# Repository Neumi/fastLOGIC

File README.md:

# fastLOGIC! open-source (industrial) logic controller

### An affordable Arduino-based board designed for straightforward (industrial) logic control, ideal for building small-scale automation and control solutions.
FastLOGIC! is designed to cater to the automation needs of various applications, especially those with modest logic requirements. Its purpose is to streamline smaller projects by eliminating the need for excessive error-prone breadboarding while retaining flexibility and adaptability.

Use cases could be one of these: 
- a programmable fridge controller
- water level-dependent pump controller
- a timer that is triggered by a button
- an actuator that activates and moves to an end stop upon receiving a triggering input
- some sensor data you need to display
- a water level sensor/alarm
- you get the idea

# Software

The Arduino [library](https://github.com/Neumi/fastLOGIC/tree/main/software/library/fastLOGIC) can be used to get started. A few example sketches show what fastLOGIC! is capable of, how to read sensor data and how to write outputs to the LEDs and relays.

The library covers most cases, but if you want to write or read directly from or to the pins:
```cpp
// fastLOGIC! pin mapping
DIGITAL_IN_A = D2;
DIGITAL_IN_B = D3;
RELAY_A_OUT = D5;
RELAY_B_OUT = D4;
TM1637_SCK = D6;
TM1637_DIO = D7;
DS18B20_DATA = D9;
LED_B_OUT = D10;
LED_A_OUT = D13;
VOLTAGE_SENS_IN = A0;
BUTTONS_IN = A1;
ANALOG_IN_A = A2;
ANALOG_IN_B = A3;
```

If you want to use the **7-segment display**, use this [library](https://github.com/avishorp/TM1637).

The part numbers in the KiCAD files are LCSC part numbers. This means you can order directly from JLCPCB using the manufacturing files in the [production folder](https://github.com/Neumi/fastLOGIC/tree/main/hardware/version001/fastLOGIC/production).
I typically opt for SMT parts exclusively due to the high cost associated with THT assembly and also because not all the required parts are readily available in stock.

# Hardware
The placement is largely self-explanatory. If you find yourself uncertain, you can refer to the images provided below or utilize the 3D view feature in KiCAD for further clarification.

###  The only hardware parts you need:
- [relais 5V](https://de.aliexpress.com/item/1005006065653383.html)
- [4-bit Common Anode Display](https://de.aliexpress.com/item/1005006101748128.html)
- [JST connectors 3pin + 4pin](https://de.aliexpress.com/item/4000120545240.html)
- [Screw terminals 2pin + 3pin](https://de.aliexpress.com/item/1005005194957825.html)
- [USB connector Type A](https://de.aliexpress.com/item/1005004679855929.html)
- [Case](https://de.aliexpress.com/item/32760647473.html)
- an [ISP](https://de.aliexpress.com/item/1005006164091737.html) or Arduino in ISP mode to burn the Bootloader
- three 5mm (M3) screws

### Optional:
- [XGZP6847a pressure sensor](https://de.aliexpress.com/item/1005003768236942.html)
- [High-pressure sensor](https://de.aliexpress.com/item/1005005510454084.html)
- [DS18B20 temperature sensor](https://de.aliexpress.com/item/1005005973956237.html)

## Assembly

## Video:

Follow the project on [hackaday.io](https://hackaday.io/project/194762-fastlogic-open-source-industrial-logic-control)!

### Enjoy the project, but keep in mind:
* **The project is still under development and is currently in the prototype stage! Keep an eye out for updates!**
* **This also implies that not all functions are guaranteed to work flawlessly and may not be entirely safe**
* **Avoid unsupervised usage in a production environment. Utilize at your own risk**
* **Ensure input voltage is between the range of 12 to 25V. (Currently lacking reverse polarity protection)**
* **Do not use the relay to switch mains voltage! It's suitable only for low voltage and currents below 5A**

### Happy building + coding!

## Big thanks to the sponsors of this project!

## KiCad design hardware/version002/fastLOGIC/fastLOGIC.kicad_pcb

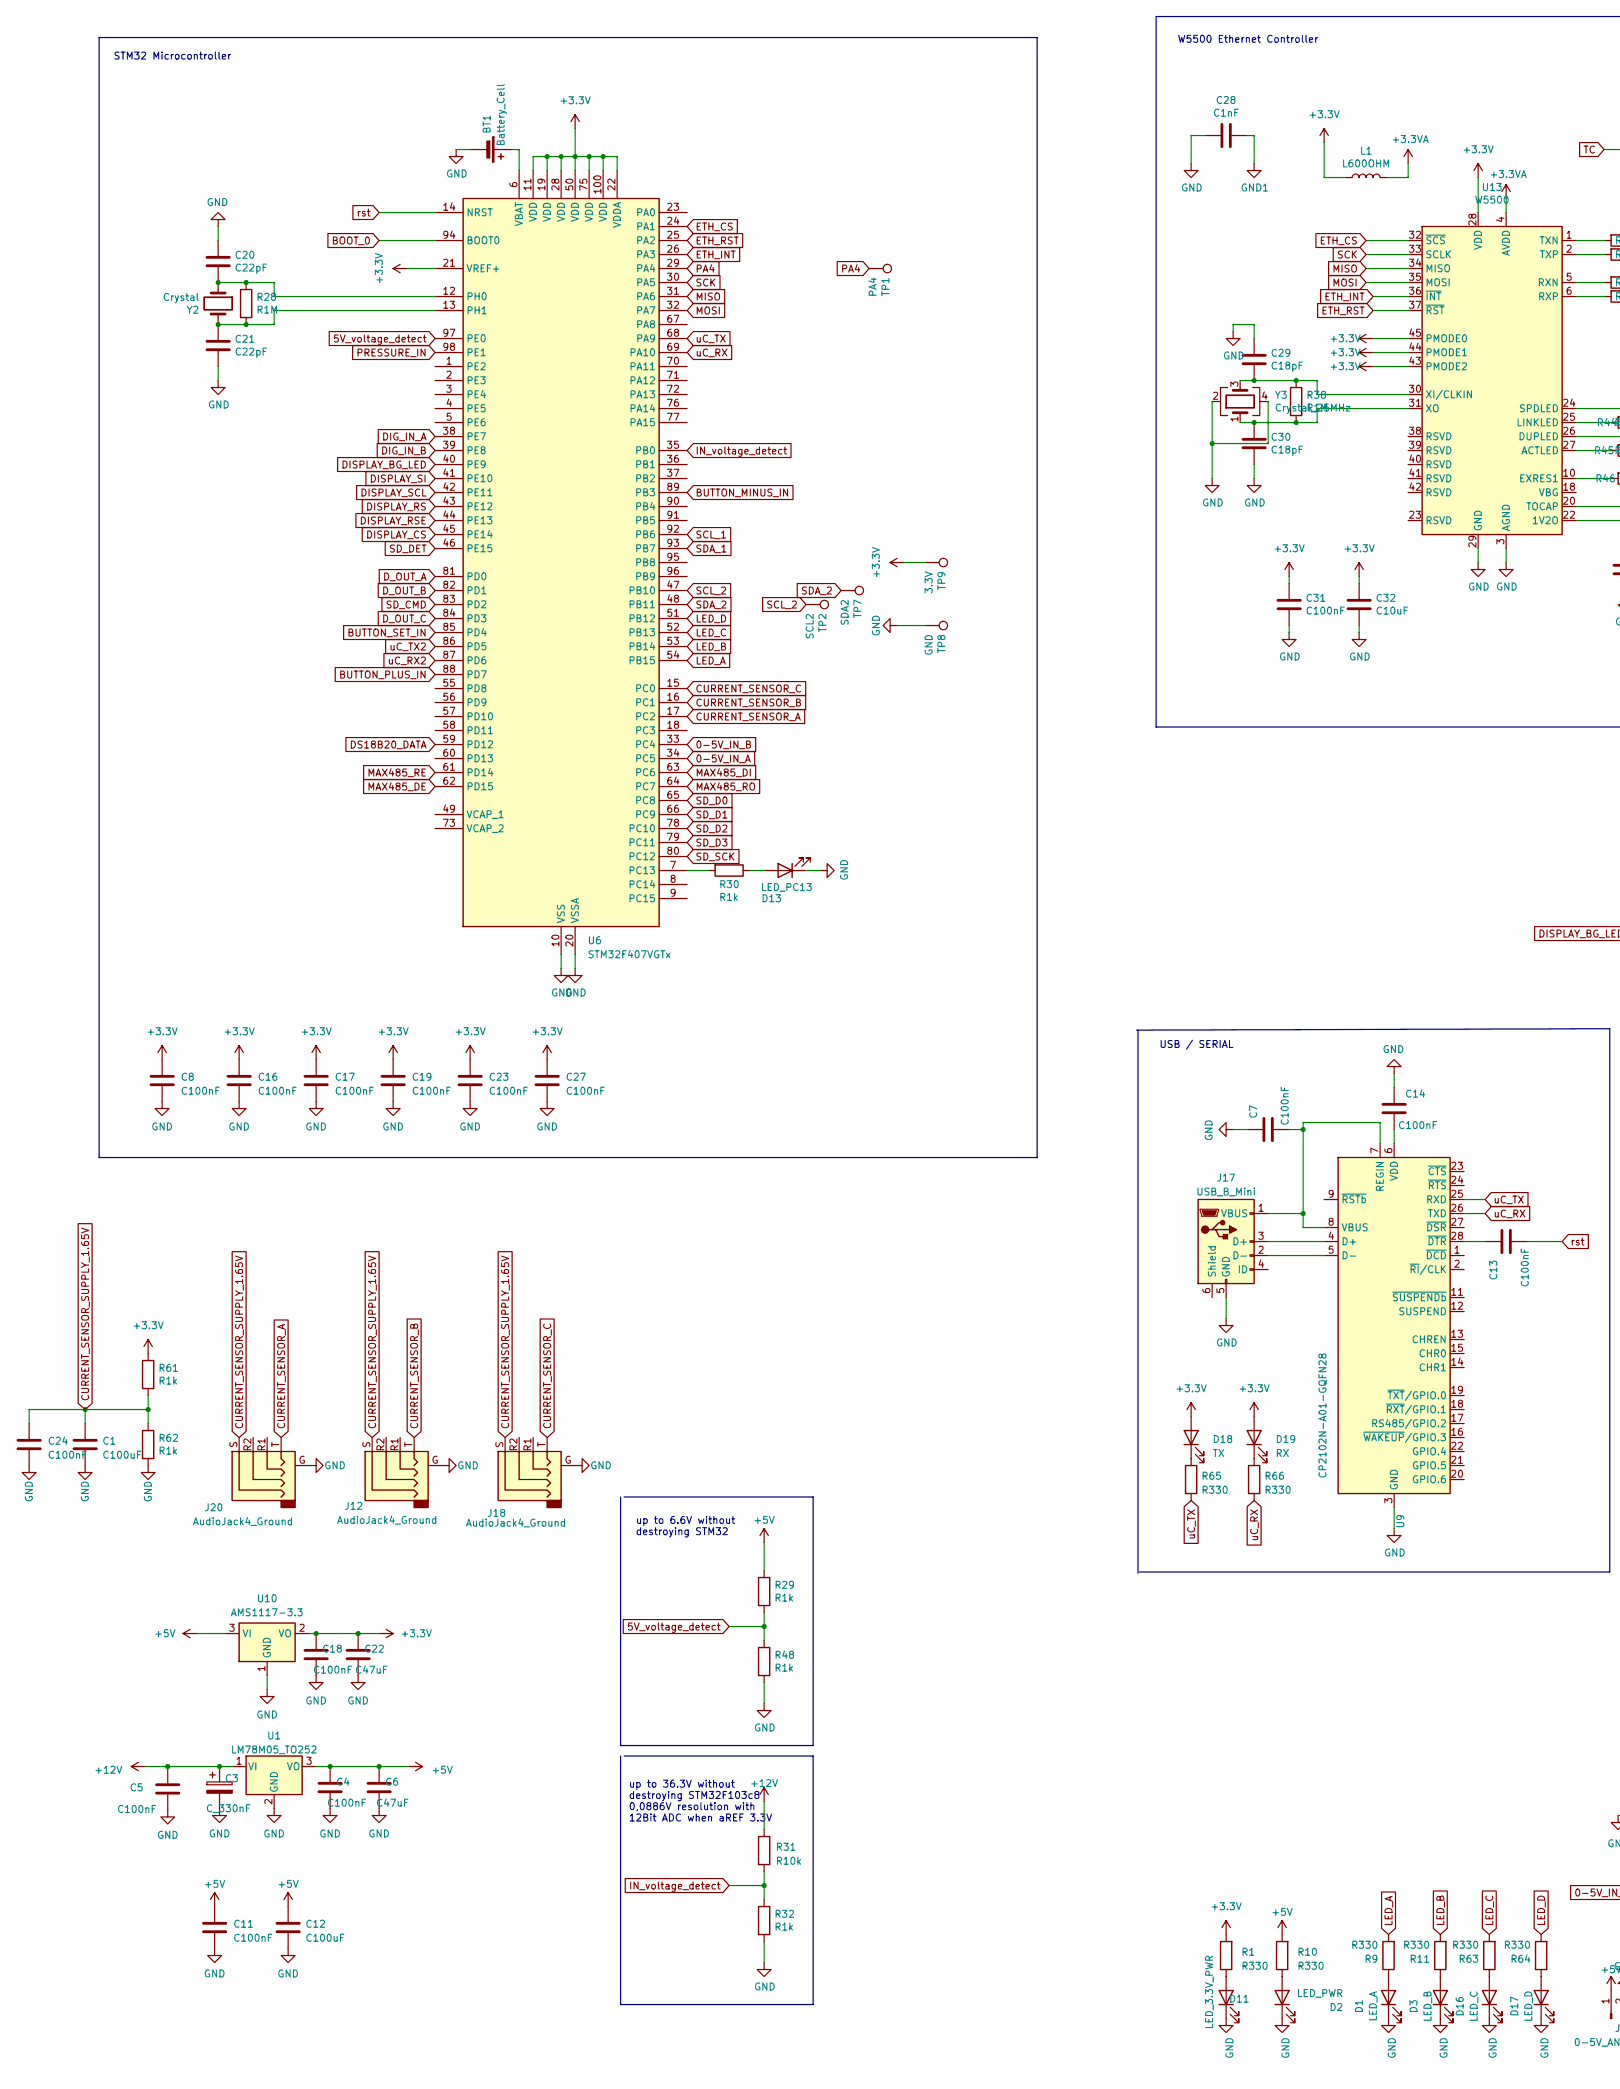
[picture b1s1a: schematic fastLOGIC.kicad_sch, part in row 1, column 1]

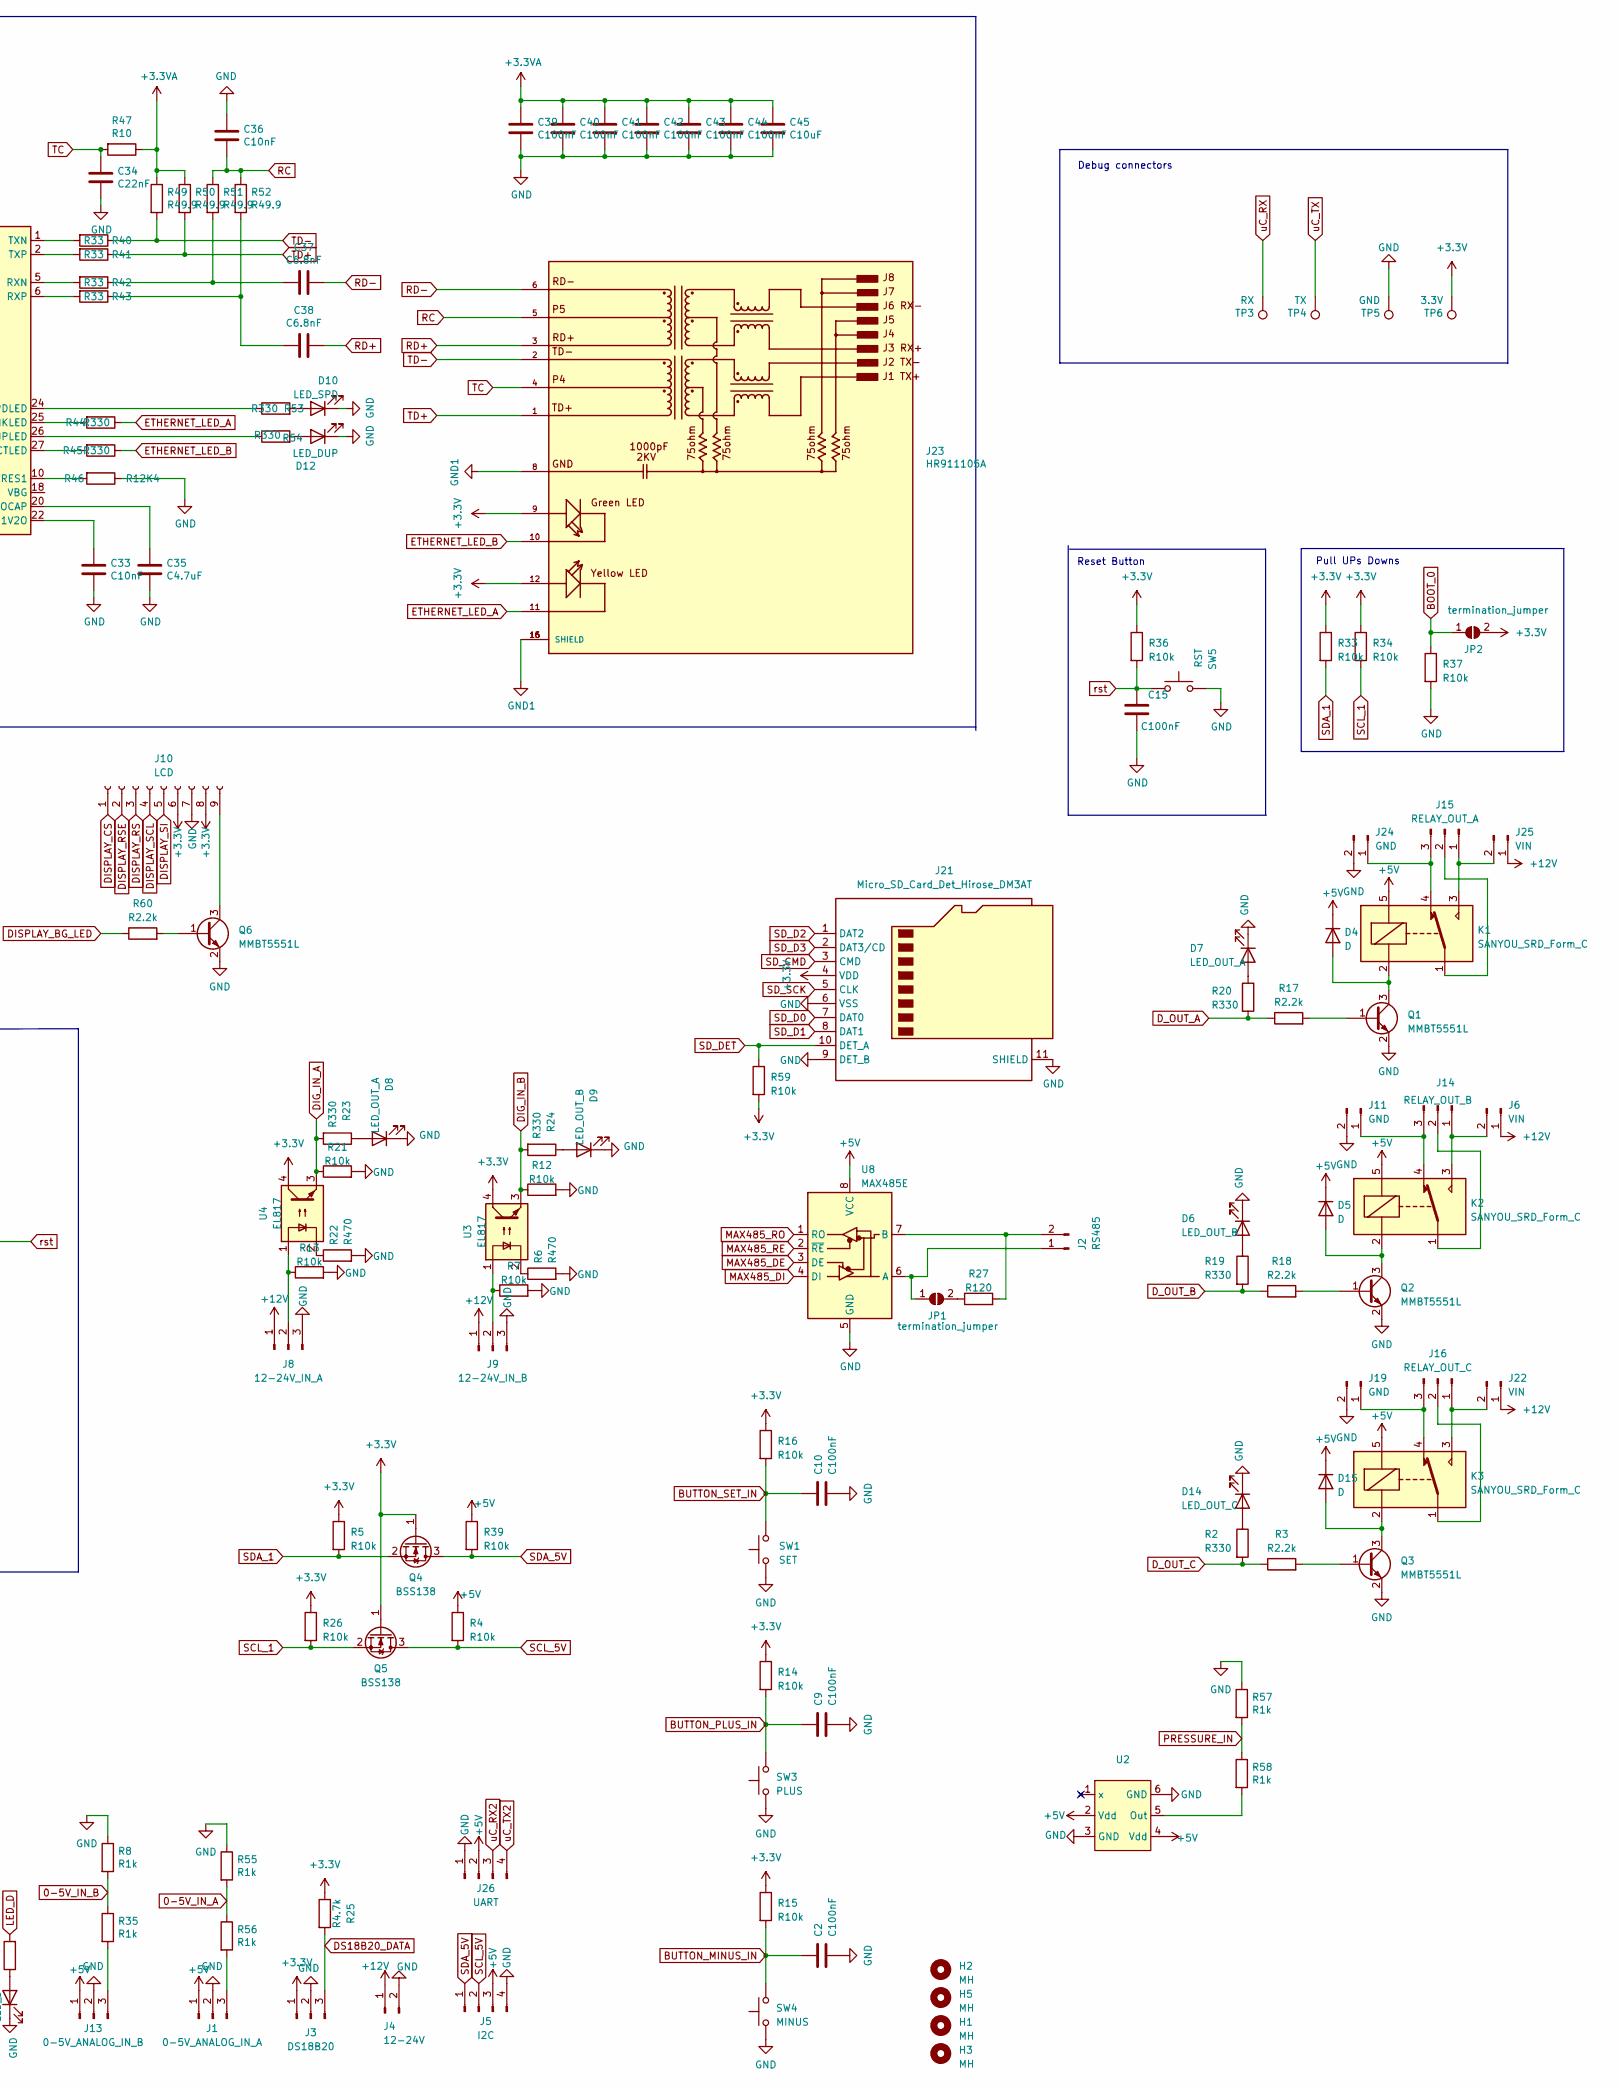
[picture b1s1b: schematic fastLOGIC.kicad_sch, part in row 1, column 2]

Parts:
BT1: Battery_Cell; BatteryHolder_Keystone_1060_1x2032; LCSC C70377
C1, C12: C100uF; C_1206_3216Metric; LCSC C15008
C2, C7, C8, C9, C10, C11, C13, C14, C15, C16, C17, C19, C23, C24, C27, C31: C100nF; C_0603_1608Metric; LCSC C14663
C3: C_330nF; CP_Elec_4x5.4; LCSC C264238
C4, C5, C18: C100nF; C_1206_3216Metric; LCSC C24497
C6, C22: C47uF; C_1206_3216Metric; LCSC C96123
C20, C21: C22pF; C_0402_1005Metric; LCSC C1555
C28: C1nF; C_1206_3216Metric; LCSC C9196
C29, C30: C18pF; C_0402_1005Metric; LCSC C1549
C32, C45: C10uF; C_0805_2012Metric; LCSC C15850
C33: C10nF; C_0402_1005Metric; LCSC C15195
C34: C22nF; C_0603_1608Metric; LCSC C21122
C35: C4.7uF; C_0402_1005Metric; LCSC C23733
C36: C10nF; C_0603_1608Metric; LCSC C57112
C37, C38: C6.8nF; C_0402_1005Metric; LCSC C1542
C39, C40, C41, C42, C43, C44: C100nF; C_0402_1005Metric; LCSC C307331
D1: LED_A; LED_0805_2012Metric; LCSC C2297
D2: LED_PWR; LED_0805_2012Metric; LCSC C84256
D3: LED_B; LED_0805_2012Metric; LCSC C2297
D4, D5, D15: D; D_SMA; LCSC C22452
D6, D9: LED_OUT_B; LED_0805_2012Metric; LCSC C2296
D7, D8: LED_OUT_A; LED_0805_2012Metric; LCSC C2296
D10: LED_SPD; LED_0805_2012Metric; LCSC C2296
D11: LED_3.3V_PWR; LED_0805_2012Metric; LCSC C2296
D12: LED_DUP; LED_0805_2012Metric; LCSC C2296
D13: LED_PC13; LED_0805_2012Metric; LCSC C84256
D14: LED_OUT_C; LED_0805_2012Metric; LCSC C2296
D16: LED_C; LED_0805_2012Metric; LCSC C2297
D17: LED_D; LED_0805_2012Metric; LCSC C2297
D18: TX; LED_0805_2012Metric; LCSC C2297
D19: RX; LED_0805_2012Metric; LCSC C2297
H1, H2, H3, H5: MH; MountingHole_3.2mm_M3_DIN965
J1: 0-5V_ANALOG_IN_A; JST_EH_S3B-EH_1x03_P2.50mm_Horizontal; LCSC C157928
J2: RS485; TerminalBlock_4Ucon_1x02_P3.50mm_Vertical; LCSC C2997509
J3: DS18B20; JST_EH_S3B-EH_1x03_P2.50mm_Horizontal; LCSC C157928
J4: 12-24V; TerminalBlock_4Ucon_1x02_P3.50mm_Vertical; LCSC C2997509
J5: I2C; JST_EH_S4B-EH_1x04_P2.50mm_Horizontal; LCSC C157925
J6, J22, J25: VIN; PinHeader_1x02_P2.54mm_Vertical
J8: 12-24V_IN_A; TerminalBlock_4Ucon_1x03_P3.50mm_Vertical; LCSC C2997510
J9: 12-24V_IN_B; TerminalBlock_4Ucon_1x03_P3.50mm_Vertical; LCSC C2997510
J10: LCD; LCD_GMG12864-06D
J11, J19, J24: GND; PinHeader_1x02_P2.54mm_Vertical
J12, J18, J20: AudioJack4_Ground; Jack_3.5mm_PJ320E_Horizontal
J13: 0-5V_ANALOG_IN_B; JST_EH_S3B-EH_1x03_P2.50mm_Horizontal; LCSC C157928
J14: RELAY_OUT_B; TerminalBlock_4Ucon_1x03_P3.50mm_Vertical; LCSC C2997510
J15: RELAY_OUT_A; TerminalBlock_4Ucon_1x03_P3.50mm_Vertical; LCSC C2997510
J16: RELAY_OUT_C; TerminalBlock_4Ucon_1x03_P3.50mm_Vertical; LCSC C2997510
J17: USB_B_Mini; USB_Mini-B_Tensility_54-00023_Vertical; LCSC C6331167
J21: Micro_SD_Card_Det_Hirose_DM3AT; microSD_HC_Hirose_DM3AT-SF-PEJM5; LCSC C114218
J23: HR911105A; RJ45_Hanrun_HR911105A_Horizontal; PARTREV A; LCSC C12074
J26: UART; JST_EH_B4B-EH-A_1x04_P2.50mm_Vertical; LCSC C157925
JP1, JP2: termination_jumper; PinHeader_1x02_P2.54mm_Vertical
K1, K2, K3: SANYOU_SRD_Form_C; Relay_SPDT_SANYOU_SRD_Series_Form_C; LCSC C35449
L1: L600OHM; L_0805_2012Metric; LCSC C1017
Q1, Q2, Q3, Q6: MMBT5551L; SOT-23; LCSC C2145
Q4, Q5: BSS138; SOT-23; LCSC C112239
R1, R2, R9, R10, R11, R19, R20, R23, R24, R44, R45, R53, R54, R63, R64, R65, R66: R330; R_0603_1608Metric; LCSC C23138
R3, R17, R18, R60: R2.2k; R_0603_1608Metric; LCSC C4190
R4, R5, R7, R12, R13, R14, R15, R16, R21, R26, R31, R33, R34, R36, R37, R39, R59: R10k; R_0603_1608Metric; LCSC C25804
R6, R22: R470; R_0603_1608Metric; LCSC C23179
R8, R29, R30, R32, R35, R48, R55, R56, R57, R58, R61, R62: R1k; R_0603_1608Metric; LCSC C21190
R25: R4.7k; R_0603_1608Metric; LCSC C23162
R27: R120; R_0805_2012Metric; LCSC C17437
R28, R38: R1M; R_0402_1005Metric; LCSC C26083
R40, R41, R42, R43: R33; R_0603_1608Metric; LCSC C23140
R46: R12K4; R_0603_1608Metric; LCSC C22865
R47: R10; R_0603_1608Metric; LCSC C22859
R49, R50, R51, R52: R49.9; R_0603_1608Metric; LCSC C23185
SW1: SET; SW_Push_1P1T_NO_CK_KSC7xxJ; LCSC C318884
SW3: PLUS; SW_Push_1P1T_NO_CK_KSC7xxJ; LCSC C318884
SW4: MINUS; SW_Push_1P1T_NO_CK_KSC7xxJ; LCSC C318884
SW5: RST; SW_Push_1P1T_NO_CK_KSC7xxJ; LCSC C318884
TP1: PA4; TestPoint_Pad_D2.0mm
TP2: SCL2; TestPoint_Pad_D2.0mm
TP3: RX; TestPoint_Pad_D2.0mm
TP4: TX; TestPoint_Pad_D2.0mm
TP5, TP8: GND; TestPoint_Pad_D2.0mm
TP6, TP9: 3.3V; TestPoint_Pad_D2.0mm
TP7: SDA2; TestPoint_Pad_D2.0mm
U1: LM78M05_TO252; TO-252-2; LCSC C58069
U2: XGZP6847A
U3, U4: EL817; DIP-4_W8.89mm_SMDSocket_LongPads; LCSC C106900
U6: STM32F407VGTx; LQFP-100_14x14mm_P0.5mm; LCSC C12345
U8: MAX485E; SOP-8_3.9x4.9mm_P1.27mm; LCSC C481667
U9: CP2102N-A01-GQFN28; QFN-28-1EP_5x5mm_P0.5mm_EP3.35x3.35mm; LCSC C6568
U10: AMS1117-3.3; SOT-223-3_TabPin2; LCSC C6186
U13: W5500; LQFP-48_7x7mm_P0.5mm; LCSC C32843
Y2: Crystal; Crystal_SMD_5032-2Pin_5.0x3.2mm; LCSC C115962
Y3: Crystal_25MHz; Crystal_SMD_3225-4Pin_3.2x2.5mm; LCSC C9006

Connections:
0-5V_IN_A: R55.2, R56.1, U6.34 (PC5)
0-5V_IN_B: R8.2, R35.1, U6.33 (PC4)
5V_voltage_detect: R29.2, R48.1, U6.97 (PE0)
+3.3V: C8.1, C16.1, C17.1, C18.1, C19.1, C22.1, C23.1, C27.1, C31.1, C32.1, D18.2 (A), D19.2 (A), J3.1, J10.6, J10.8, J21.4 (VDD), J23.9, J23.12, JP2.2 (B), L1.1, Q4.1 (G), Q5.1 (G), R1.2, R5.1, R14.1, R15.1, R16.1, R25.1, R26.1, R33.1, R34.1, R36.1, R59.2, R61.1, TP6.1, TP9.1, U3.4, U4.4, U6.11 (VDD), U6.19 (VDD), U6.21 (VREF+), U6.22 (VDDA), U6.28 (VDD), U6.50 (VDD), U6.75 (VDD), U6.100 (VDD), U10.2 (VO), U13.28 (VDD), U13.43 (PMODE2), U13.44 (PMODE1), U13.45 (PMODE0)
+3.3VA: C39.1, C40.1, C41.1, C42.1, C43.1, C44.1, C45.1, L1.2, R47.1, R49.1, R50.1, U13.4 (AVDD), U13.8 (AVDD), U13.11 (AVDD), U13.15 (AVDD), U13.17 (AVDD), U13.21 (AVDD)
+5V: C4.1, C6.1, C11.1, C12.1, D4.1 (K), D5.1 (K), D15.1 (K), J1.1, J5.3, J13.1, J26.2, K1.5, K2.5, K3.5, R4.1, R10.2, R29.1, R39.1, U1.3 (VO), U2.2 (Vdd), U2.4 (Vdd), U8.8 (VCC), U10.3 (VI)
+12V: C3.1, C5.1, J4.1, J6.1, J8.1, J9.1, J22.1, J25.1, R31.1, U1.1 (VI)
BOOT_0: JP2.1 (A), R37.1, U6.94 (BOOT0)
BUTTON_MINUS_IN: C2.1, R15.2, SW4.2, U6.89 (PB3)
BUTTON_PLUS_IN: C9.1, R14.2, SW3.2, U6.88 (PD7)
BUTTON_SET_IN: C10.1, R16.2, SW1.2, U6.85 (PD4)
CURRENT_SENSOR_A: J20.T, U6.17 (PC2)
CURRENT_SENSOR_B: J12.T, U6.16 (PC1)
CURRENT_SENSOR_C: J18.T, U6.15 (PC0)
CURRENT_SENSOR_SUPPLY_1.65V: C1.1, C24.1, J12.S, J18.S, J20.S, R61.2, R62.1
DIG_IN_A: R21.1, R23.2, U4.3, U6.38 (PE7)
DIG_IN_B: R12.1, R24.2, U3.3, U6.39 (PE8)
DISPLAY_BG_LED: R60.1, U6.40 (PE9)
DISPLAY_CS: J10.1, U6.45 (PE14)
DISPLAY_RS: J10.3, U6.43 (PE12)
DISPLAY_RSE: J10.2, U6.44 (PE13)
DISPLAY_SCL: J10.4, U6.42 (PE11)
DISPLAY_SI: J10.5, U6.41 (PE10)
DS18B20_DATA: J3.3, R25.2, U6.59 (PD12)
D_OUT_A: R17.1, R20.2, U6.81 (PD0)
D_OUT_B: R18.1, R19.2, U6.82 (PD1)
D_OUT_C: R2.2, R3.1, U6.84 (PD3)
ETHERNET_LED_A: J23.11, R44.1
ETHERNET_LED_B: J23.10, R45.1
ETH_CS: U6.24 (PA1), U13.32 (~SCS)
ETH_INT: U6.26 (PA3), U13.36 (~INT)
ETH_RST: U6.25 (PA2), U13.37 (~RST)
GND: BT1.2 (-), C1.2, C2.2, C3.2, C4.2, C5.2, C6.2, C7.1, C8.2, C9.2, C10.2, C11.2, C12.2, C14.1, C15.2, C16.2, C17.2, C18.2, C19.2, C20.1, C21.2, C22.2, C23.2, C24.2, C27.2, C28.2, C29.1, C30.2, C31.2, C32.2, C33.2, C34.1, C35.2, C36.1, C39.2, C40.2, C41.2, C42.2, C43.2, C44.2, C45.2, D1.1 (K), D2.1 (K), D3.1 (K), D6.1 (K), D7.1 (K), D8.1 (K), D9.1 (K), D10.1 (K), D11.1 (K), D12.1 (K), D13.1 (K), D14.1 (K), D16.1 (K), D17.1 (K), J1.2, J3.2, J4.2, J5.4, J8.3, J9.3, J10.7, J11.2, J12.G, J13.2, J17.5 (GND), J18.G, J19.2, J20.G, J21.6 (VSS), J21.9 (DET_B), J21.11 (SHIELD), J24.2, J26.1, Q1.2 (E), Q2.2 (E), Q3.2 (E), Q6.2 (E), R6.2, R7.2, R8.1, R12.2, R13.2, R21.2, R22.2, R32.2, R37.2, R46.1, R48.2, R55.1, R57.1, R62.2, SW1.1, SW3.1, SW4.1, SW5.2, TP5.1, TP8.1, U1.2 (GND), U2.3 (GND), U2.6 (GND), U6.10 (VSS), U6.20 (VSSA), U6.27 (VSS), U6.74 (VSS), U6.99 (VSS), U8.5 (GND), U9.3 (GND), U9.29 (GND), U10.1 (GND), U13.3 (AGND), U13.9 (AGND), U13.14 (AGND), U13.16 (AGND), U13.19 (AGND), U13.29 (GND), U13.48 (AGND), Y3.2, Y3.4
GND1: C28.1, J23.8, J23.15 (SHIELD), J23.16 (SHIELD)
IN_voltage_detect: R31.2, R32.1, U6.35 (PB0)
LED_A: R9.2, U6.54 (PB15)
LED_B: R11.2, U6.53 (PB14)
LED_C: R63.2, U6.52 (PB13)
LED_D: R64.2, U6.51 (PB12)
MAX485_DE: U6.62 (PD15), U8.3 (DE)
MAX485_DI: U6.63 (PC6), U8.4 (DI)
MAX485_RE: U6.61 (PD14), U8.2 (~RE)
MAX485_RO: U6.64 (PC7), U8.1 (RO)
MISO: U6.31 (PA6), U13.34 (MISO)
MOSI: U6.32 (PA7), U13.35 (MOSI)
unnamed: BT1.1 (+), U6.6 (VBAT)
unnamed: C37.2, R42.1, R51.2
unnamed: C38.2, R43.1, R52.2
unnamed: D1.2 (A), R9.1
unnamed: D2.2 (A), R10.1
unnamed: D3.2 (A), R11.1
unnamed: D4.2 (A), K1.2, Q1.3 (C)
unnamed: D5.2 (A), K2.2, Q2.3 (C)
unnamed: D6.2 (A), R19.1
unnamed: D7.2 (A), R20.1
unnamed: D8.2 (A), R23.1
unnamed: D9.2 (A), R24.1
unnamed: D10.2 (A), R53.2
unnamed: D11.2 (A), R1.1
unnamed: D12.2 (A), R54.2
unnamed: D13.2 (A), R30.1
unnamed: D14.2 (A), R2.1
unnamed: D15.2 (A), K3.2, Q3.3 (C)
unnamed: D16.2 (A), R63.1
unnamed: D17.2 (A), R64.1
unnamed: D18.1 (K), R65.1
unnamed: D19.1 (K), R66.1
unnamed: J1.3, R56.2
unnamed: J2.1, JP1.1 (A), U8.6 (A)
unnamed: J2.2, R27.2, U8.7 (B)
unnamed: J8.2, R13.1, U4.1
unnamed: J9.2, R7.1, U3.1
unnamed: J10.9, Q6.3 (C)
unnamed: J11.1, J14.3, K2.4
unnamed: J13.3, R35.2
unnamed: J6.2, J14.1, K2.3
unnamed: J14.2, K2.1
unnamed: J15.1, J25.2, K1.3
unnamed: J15.2, K1.1
unnamed: J15.3, J24.1, K1.4
unnamed: J16.1, J22.2, K3.3
unnamed: J16.2, K3.1
unnamed: J16.3, J19.1, K3.4
unnamed: J17.3 (D+), U9.4 (D+)
unnamed: J17.2 (D-), U9.5 (D-)
unnamed: C7.2, J17.1 (VBUS), U9.7 (REGIN), U9.8 (VBUS)
unnamed: JP1.2 (B), R27.1
unnamed: Q1.1 (B), R17.2
unnamed: Q2.1 (B), R18.2
unnamed: Q3.1 (B), R3.2
unnamed: Q6.1 (B), R60.2
unnamed: R6.1, U3.2
unnamed: R22.1, U4.2
unnamed: R58.2, U2.5 (Out)
unnamed: R30.2, U6.7 (PC13)
unnamed: C20.2, R28.1, U6.12 (PH0), Y2.1
unnamed: C21.1, R28.2, U6.13 (PH1), Y2.2
unnamed: C14.2, U9.6 (VDD)
unnamed: C13.1, U9.28 (~DTR)
unnamed: C33.1, U13.22 (1V2O)
unnamed: R45.2, U13.27 (ACTLED)
unnamed: R54.1, U13.26 (DUPLED)
unnamed: R46.2, U13.10 (EXRES1)
unnamed: R44.2, U13.25 (LINKLED)
unnamed: R42.2, U13.5 (RXN)
unnamed: R43.2, U13.6 (RXP)
unnamed: R53.1, U13.24 (SPDLED)
unnamed: C35.1, U13.20 (TOCAP)
unnamed: R40.2, U13.1 (TXN)
unnamed: R41.2, U13.2 (TXP)
unnamed: C29.2, R38.1, U13.30 (XI/CLKIN), Y3.3
unnamed: C30.1, R38.2, U13.31 (XO), Y3.1
PA4: TP1.1, U6.29 (PA4)
PRESSURE_IN: R57.2, R58.1, U6.98 (PE1)
RC: C36.2, J23.5, R51.1, R52.1
RD+: C38.1, J23.3
RD-: C37.1, J23.6
SCK: U6.30 (PA5), U13.33 (SCLK)
SCL_1: Q5.2 (S), R26.2, R34.2, U6.92 (PB6)
SCL_2: TP2.1, U6.47 (PB10)
SCL_5V: J5.2, Q5.3 (D), R4.2
SDA_1: Q4.2 (S), R5.2, R33.2, U6.93 (PB7)
SDA_2: TP7.1, U6.48 (PB11)
SDA_5V: J5.1, Q4.3 (D), R39.2
SD_CMD: J21.3 (CMD), U6.83 (PD2)
SD_D0: J21.7 (DAT0), U6.65 (PC8)
SD_D1: J21.8 (DAT1), U6.66 (PC9)
SD_D2: J21.1 (DAT2), U6.78 (PC10)
SD_D3: J21.2 (DAT3/CD), U6.79 (PC11)
SD_DET: J21.10 (DET_A), R59.1, U6.46 (PE15)
SD_SCK: J21.5 (CLK), U6.80 (PC12)
TC: C34.2, J23.4, R47.2
TD+: J23.1, R41.1, R50.2
TD-: J23.2, R40.1, R49.2
rst: C13.2, C15.1, R36.2, SW5.1, U6.14 (NRST)
uC_RX: R66.2, TP3.1, U6.69 (PA10), U9.26 (TXD)
uC_RX2: J26.3, U6.87 (PD6)
uC_TX: R65.2, TP4.1, U6.68 (PA9), U9.25 (RXD)
uC_TX2: J26.4, U6.86 (PD5)

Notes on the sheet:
up to 6.6V without destroying STM32
Pull UPs Downs
USB / SERIAL
Debug connectors
up to 36.3V without destroying STM32F103c8 0,0886V resolution with 12Bit ADC when aREF 3.3V
Reset Button
STM32 Microcontroller
W5500 Ethernet Controller

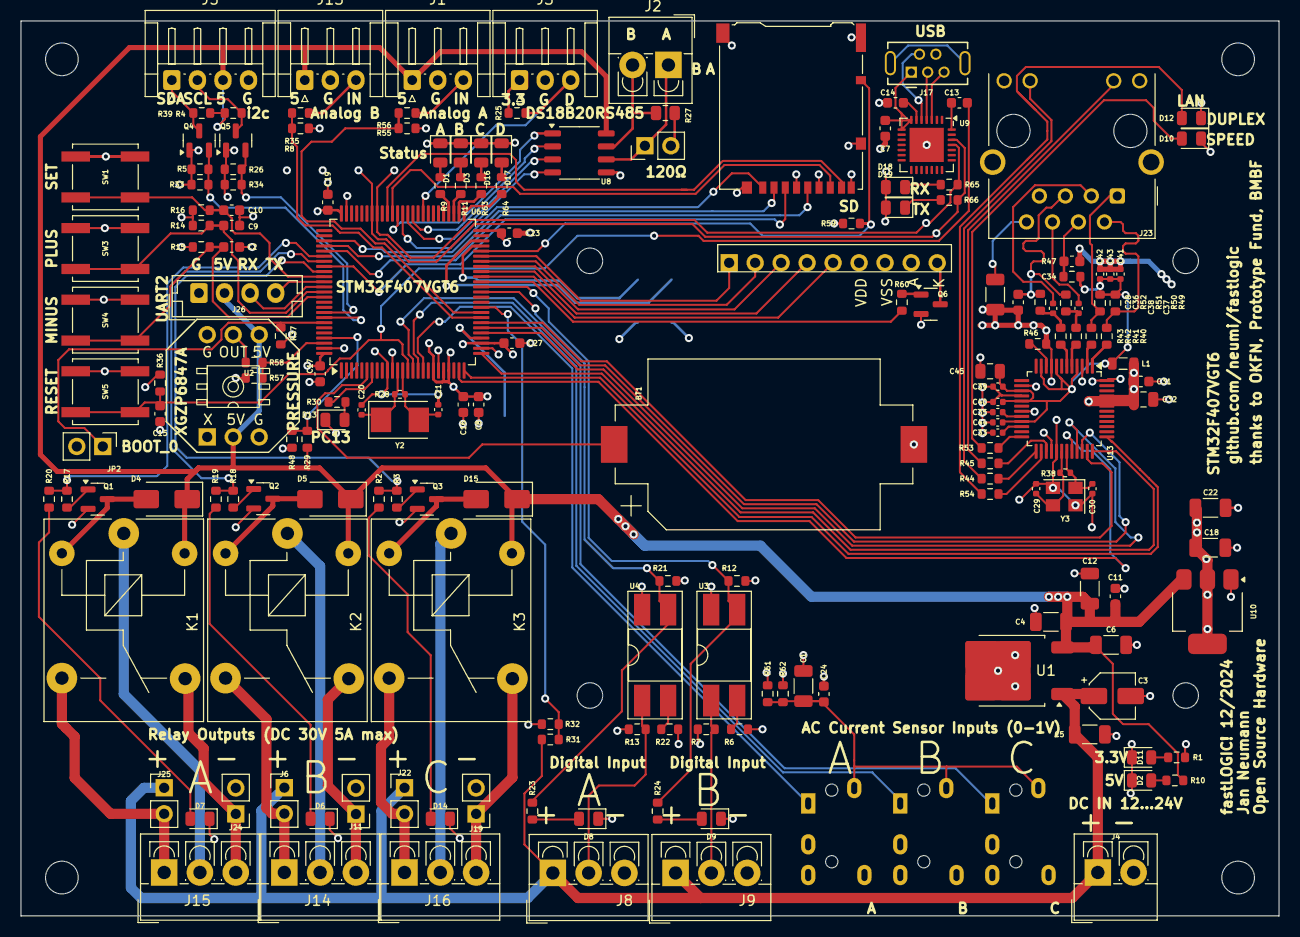
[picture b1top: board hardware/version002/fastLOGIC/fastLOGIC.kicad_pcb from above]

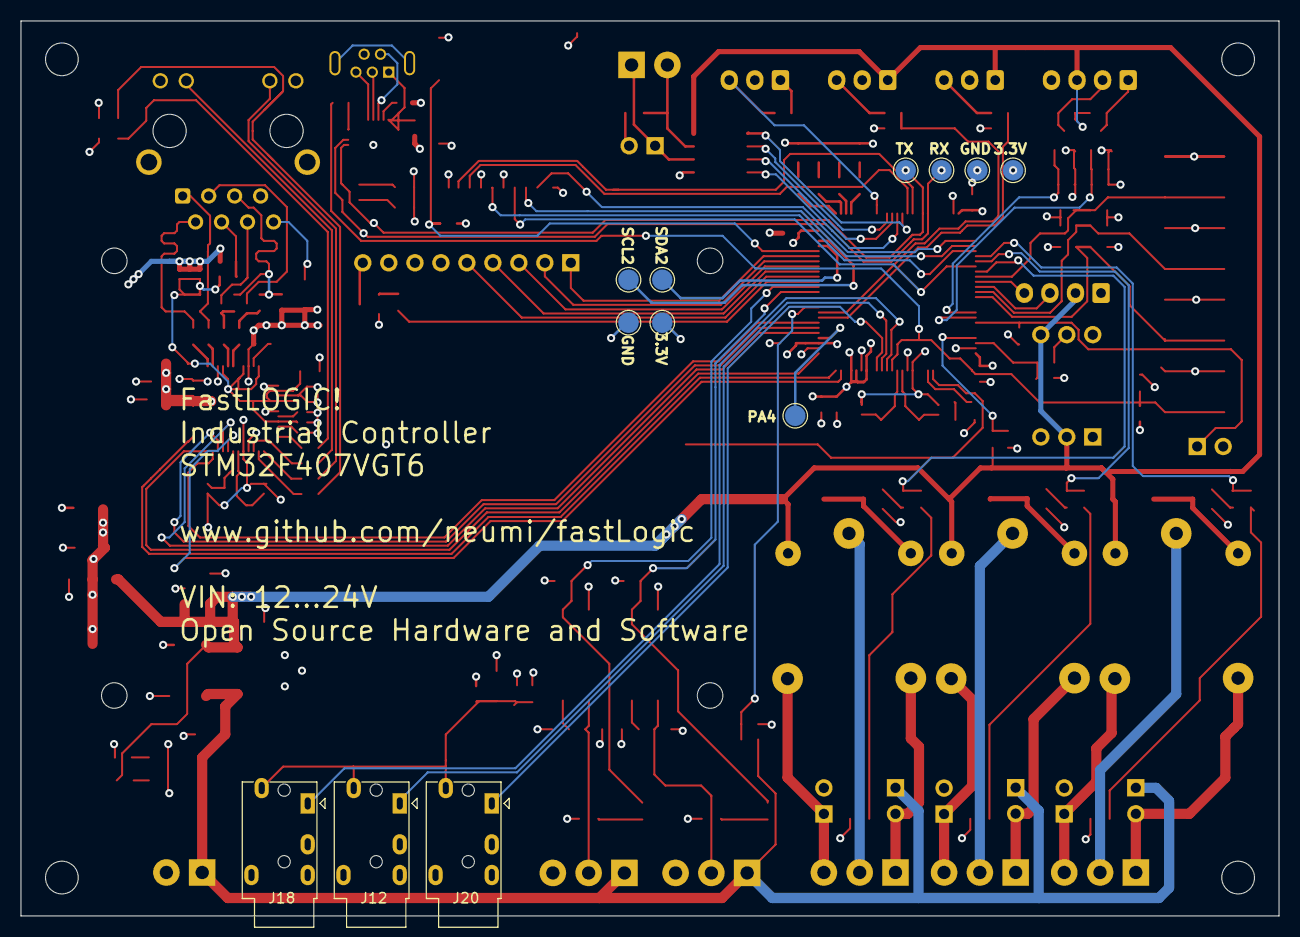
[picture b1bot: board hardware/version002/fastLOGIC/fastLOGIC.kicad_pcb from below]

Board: 4 copper layers, 123.0 x 87.5 mm, 194 parts (12 on the bottom side), 139 nets.

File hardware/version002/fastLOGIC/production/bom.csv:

Designator,Footprint,Quantity,Value,LCSC Part #
BT1,BatteryHolder_Keystone_1060_1x2032,1,Battery_Cell,C70377
"C1, C12",1206,2,C100uF,C15008
"C10, C11, C13, C14, C15, C16, C17, C19, C2, C23, C24, C27, C31, C7, C8, C9",0603,16,C100nF,C14663
"C18, C4, C5",1206,3,C100nF,C24497
"C20, C21",0402,2,C22pF,C1555
"C22, C6",1206,2,C47uF,C96123
C28,1206,1,C1nF,C9196
"C29, C30",0402,2,C18pF,C1549
C3,CP_Elec_4x5.4,1,C_330nF,C264238
"C32, C45",0805,2,C10uF,C15850
C33,0402,1,C10nF,C15195
C34,0603,1,C22nF,C21122
C35,0402,1,C4.7uF,C23733
C36,0603,1,C10nF, C57112
"C37, C38",0402,2,C6.8nF,C1542
"C39, C40, C41, C42, C43, C44",0402,6,C100nF,C307331
D1,0805,1,LED_A,C2297
D10,0805,1,LED_SPD,C2296
D11,0805,1,LED_3.3V_PWR,C2296
D12,0805,1,LED_DUP,C2296
D13,0805,1,LED_PC13,C84256
D14,0805,1,LED_OUT_C,C2296
"D15, D4, D5",D_SMA,3,D,C22452
D16,0805,1,LED_C,C2297
D17,0805,1,LED_D,C2297
D18,0805,1,TX,C2297
D19,0805,1,RX,C2297
D2,0805,1,LED_PWR,C84256
D3,0805,1,LED_B,C2297
"D6, D9",0805,2,LED_OUT_B,C2296
"D7, D8",0805,2,LED_OUT_A,C2296
"H1, H2, H3, H5",MountingHole_3.2mm_M3_DIN965,4,MH,
J1,JST_EH_S3B-EH_1x03_P2.50mm_Horizontal,1,0-5V_ANALOG_IN_A,C157928
J10,LCD_GMG12864-06D,1,LCD,
"J11, J19, J24",PinHeader_1x02_P2.54mm_Vertical,3,GND,
"J12, J18, J20",Jack_3.5mm_PJ320E_Horizontal,3,AudioJack4_Ground,
J13,JST_EH_S3B-EH_1x03_P2.50mm_Horizontal,1,0-5V_ANALOG_IN_B,C157928
J14,TerminalBlock_4Ucon_1x03_P3.50mm_Vertical,1,RELAY_OUT_B,C2997510
J15,TerminalBlock_4Ucon_1x03_P3.50mm_Vertical,1,RELAY_OUT_A,C2997510
J16,TerminalBlock_4Ucon_1x03_P3.50mm_Vertical,1,RELAY_OUT_C,C2997510
J17,USB_Mini-B_Tensility_54-00023_Vertical,1,USB_B_Mini,C6331167
J2,TerminalBlock_4Ucon_1x02_P3.50mm_Vertical,1,RS485,C2997509
J21,microSD_HC_Hirose_DM3AT-SF-PEJM5,1,Micro_SD_Card_Det_Hirose_DM3AT,C114218
"J22, J25, J6",PinHeader_1x02_P2.54mm_Vertical,3,VIN,
J23,RJ45_Hanrun_HR911105A_Horizontal,1,HR911105A,C12074
J26,JST_EH_B4B-EH-A_1x04_P2.50mm_Vertical,1,UART,C157925
J3,JST_EH_S3B-EH_1x03_P2.50mm_Horizontal,1,DS18B20,C157928
J4,TerminalBlock_4Ucon_1x02_P3.50mm_Vertical,1,12-24V,C2997509
J5,JST_EH_S4B-EH_1x04_P2.50mm_Horizontal,1,I2C,C157925
J8,TerminalBlock_4Ucon_1x03_P3.50mm_Vertical,1,12-24V_IN_A,C2997510
J9,TerminalBlock_4Ucon_1x03_P3.50mm_Vertical,1,12-24V_IN_B,C2997510
"JP1, JP2",PinHeader_1x02_P2.54mm_Vertical,2,termination_jumper,
"K1, K2, K3",Relay_SPDT_SANYOU_SRD_Series_Form_C,3,SANYOU_SRD_Form_C,C35449
L1,0805,1,L600OHM,C1017
"Q1, Q2, Q3, Q6",SOT-23,4,MMBT5551L,C2145
"Q4, Q5",SOT-23,2,BSS138,C112239
"R1, R10, R11, R19, R2, R20, R23, R24, R44, R45, R53, R54, R63, R64, R65, R66, R9",0603,17,R330,C23138
"R12, R13, R14, R15, R16, R21, R26, R31, R33, R34, R36, R37, R39, R4, R5, R59, R7",0603,17,R10k,C25804
"R17, R18, R3, R60",0603,4,R2.2k,C4190
"R22, R6",0603,2,R470,C23179
R25,0603,1,R4.7k,C23162
R27,0805,1,R120,C17437
"R28, R38",0402,2,R1M,C26083
"R29, R30, R32, R35, R48, R55, R56, R57, R58, R61, R62, R8",0603,12,R1k,C21190
"R40, R41, R42, R43",0603,4,R33,C23140
R46,0603,1,R12K4,C22865
R47,0603,1,R10,C22859
"R49, R50, R51, R52",0603,4,R49.9,C23185
SW1,SW_Push_1P1T_NO_CK_KSC7xxJ,1,SET,C318884
SW3,SW_Push_1P1T_NO_CK_KSC7xxJ,1,PLUS,C318884
SW4,SW_Push_1P1T_NO_CK_KSC7xxJ,1,MINUS,C318884
SW5,SW_Push_1P1T_NO_CK_KSC7xxJ,1,RST,C318884
TP1,TestPoint_Pad_D2.0mm,1,PA4,
TP2,TestPoint_Pad_D2.0mm,1,SCL2,
TP3,TestPoint_Pad_D2.0mm,1,RX,
TP4,TestPoint_Pad_D2.0mm,1,TX,
"TP5, TP8",TestPoint_Pad_D2.0mm,2,GND,
"TP6, TP9",TestPoint_Pad_D2.0mm,2,3.3V,
TP7,TestPoint_Pad_D2.0mm,1,SDA2,
U1,TO-252-2,1,LM78M05_TO252,C58069
U10,SOT-223-3_TabPin2,1,AMS1117-3.3,C6186
U13,LQFP-48_7x7mm_P0.5mm,1,W5500, C32843
U2,XGZP6847A,1,~,
"U3, U4",DIP-4_W8.89mm_SMDSocket_LongPads,2,EL817,C106900
U6,LQFP-100_14x14mm_P0.5mm,1,STM32F407VGTx,C12345
U8,SOP-8_3.9x4.9mm_P1.27mm,1,MAX485E,C481667
U9,QFN-28-1EP_5x5mm_P0.5mm_EP3.35x3.35mm,1,CP2102N-A01-GQFN28,C6568
Y2,Crystal_SMD_5032-2Pin_5.0x3.2mm,1,Crystal,C115962
Y3,Crystal_SMD_3225-4Pin_3.2x2.5mm,1,Crystal_25MHz,C9006
